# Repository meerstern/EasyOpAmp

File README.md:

# EasyOpAmp
Breakout board for OpAmp 

EasyOpAmpボードはsoic8の2回路入りオペアンプを2.54ピッチに変換するブレイクアウトボードです。  
ボード上にオペアンプの図が書かれているため、試作や実験の際に誤配線防止やデータシートの参照が不要になります。  
なお、ブレッドボード上の配線を綺麗にするため、一般的なオペアンプのピン配置と異なり、2つオペアンプが並列に並んだピン配置となっています。  

MIT Lisense

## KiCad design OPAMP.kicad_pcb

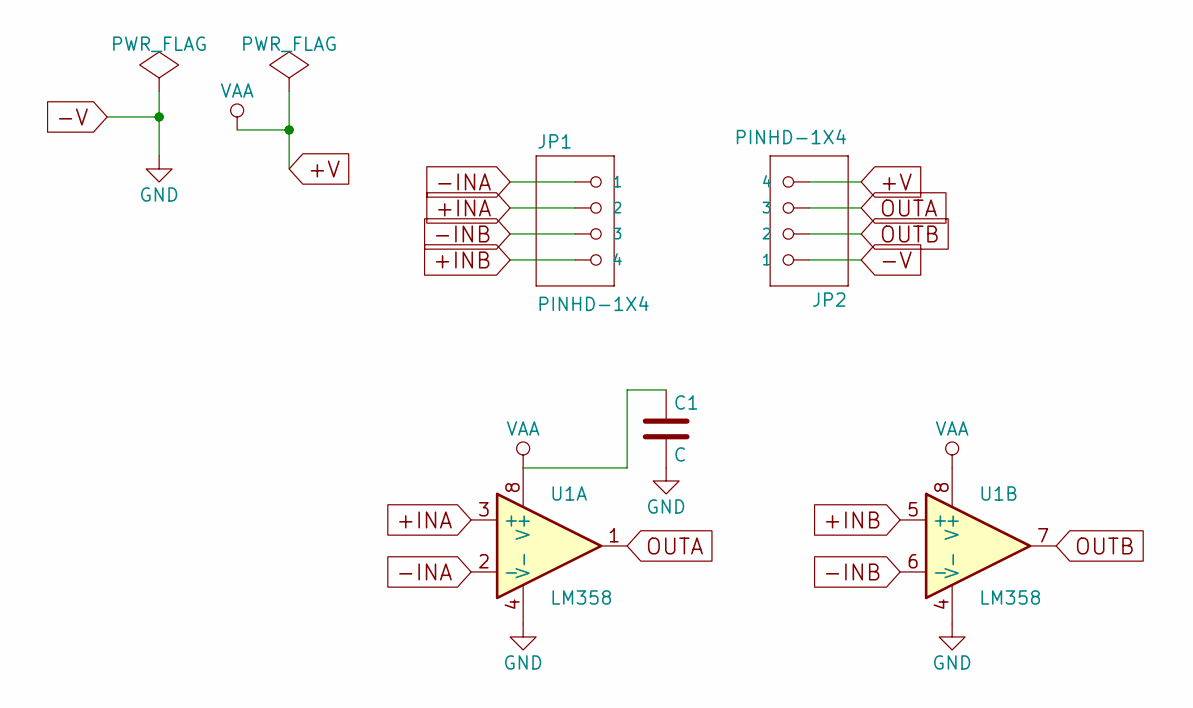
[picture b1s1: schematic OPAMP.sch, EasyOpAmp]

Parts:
C1: C; generic-SMD1608
JP1, JP2: PINHD-1X4; pinhead-1X04
U1: LM358; SOIC8

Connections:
+INA: JP1.2, U1.3 (+)
+INB: JP1.4, U1.5 (+)
+V: C1.1, JP2.4, U1.8 (V+)
-INA: JP1.1, U1.2 (-)
-INB: JP1.3, U1.6 (-)
-V: C1.2, JP2.1, U1.4 (V-)
OUTA: JP2.3, U1.1
OUTB: JP2.2, U1.7

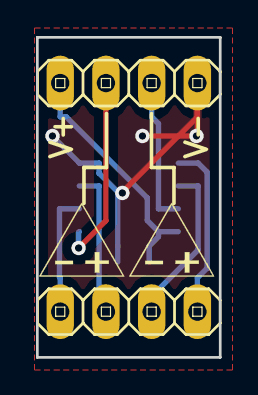
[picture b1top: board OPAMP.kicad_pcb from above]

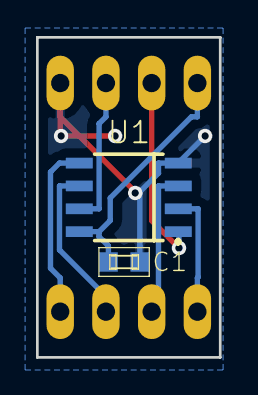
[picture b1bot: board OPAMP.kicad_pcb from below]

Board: 2 copper layers, 10.2 x 17.8 mm, 6 parts (2 on the bottom side), 8 nets.

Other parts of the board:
G1, G2: LOGO; opamp2

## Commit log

2019-01-06 Init submit
